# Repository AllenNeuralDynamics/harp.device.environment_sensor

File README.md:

A self-contained, harp-compliant environment sensor

## Features
* pressure sensing
* temperature sensing
* humidity sensing
* USB powered
* Harp synchronization input

## Wiring Diagram
TODO

### Device Pinout
TODO

### Wiring Diagram
TODO

## Theory of Operation
TODO: awesome diagram {here}

## Harp Register Map
[List of Registers](./firmware/docs/register_map.csv)

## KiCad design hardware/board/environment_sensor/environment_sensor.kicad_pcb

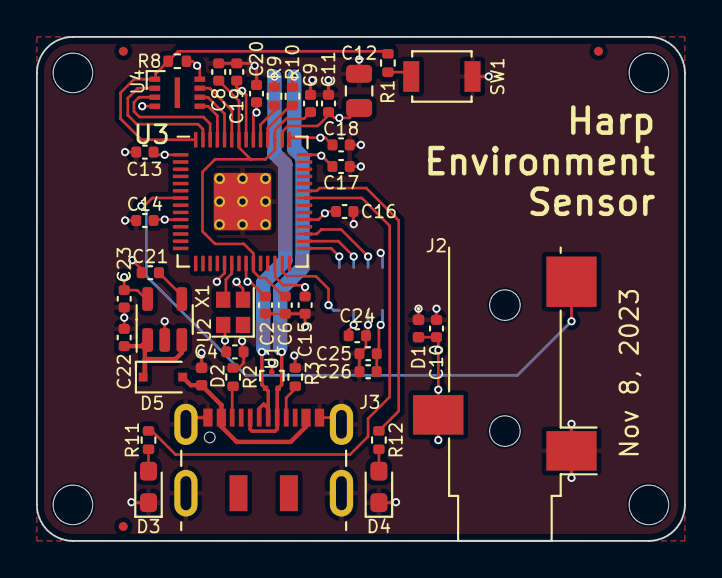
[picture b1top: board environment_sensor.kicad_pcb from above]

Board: 4 copper layers, 36.0 x 28.0 mm, 47 parts (1 on the bottom side), 29 nets.

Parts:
C2, C6, C8, C13, C14, C15, C16, C17, C18, C19, C20, C24, C25: 100nF; C_0402_1005Metric
C4, C21: 10nF; C_0402_1005Metric
C9, C10, C11, C22, C26: 1uF; C_0402_1005Metric
C12: 10uF; C_0805_2012Metric
C23: 2.2uF; C_0402_1005Metric
D1, D2: D_TVS; D_0402_1005Metric
D3, D4: LED; LED_0603_1608Metric_Pad1.05x0.95mm_HandSolder
D5: BAT54J; D_SOD-323F
FID1, FID2, FID3: Fiducial; Fiducial_0.5mm_Mask1mm
J2: AudioJack3; Jack_3.5mm_CUI_SJ-3523-SMT_Horizontal
J3: USB_C_Receptacle_USB2.0; USB_C_Receptacle_JAE_DX07S016JA1R1500
R1: 1K; R_0402_1005Metric
R2, R3: 5K1; R_0402_1005Metric
R8: 10K; R_0402_1005Metric
R9, R10: 27; R_0402_1005Metric
R11, R12: 330; R_0402_1005Metric
SW1: SW_Push; SW_SPST_B3U-1000P
U1: TPD2EUSB30; Texas_DRT-3
U2: LP2985-3.3; SOT-23-5
U3: RP2040; RP2040-QFN-56
U4: W25Q16JVUXIQ; Winbond-8USON-2x3mm
U5: BME688; Bosch_LGA-8_3x3mm_P0.8mm_ClockwisePinNumbering
X1: ECS-TXO-2016; Crystal_SMD_2016-4Pin_2.0x1.6mm

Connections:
+1V1: C6.2, C8.2, C9.1, U3.23 (DVDD), U3.45 (VREG_VOUT), U3.50 (DVDD)
+3V3: C2.2, C4.2, C10.1, C11.1, C12.1, C13.2, C14.2, C15.2, C16.2, C17.2, C18.2, C19.2, C20.2, C23.2, C24.2, C25.2, C26.1, D1.2 (A2), J2.R, R8.2, U2.5 (VOUT), U3.1 (IOVDD), U3.10 (IOVDD), U3.22 (IOVDD), U3.26 (RUN), U3.33 (IOVDD), U3.42 (IOVDD), U3.43 (ADC_AVDD), U3.44 (VREG_IN), U3.48 (USB_VDD), U3.49 (IOVDD), U4.8 (VCC), U5.6 (VDDIO), U5.8 (VDD), X1.4 (VDD)
/Harp Core RP2040 + USB/CS: U3.31 (GPIO20), U5.2 (CSB)
/Harp Core RP2040 + USB/D+: J3.A6 (D+), J3.B6 (D+), R9.2, U1.1 (D+)
/Harp Core RP2040 + USB/D-: J3.A7 (D-), J3.B7 (D-), R10.2, U1.2 (D-)
/Harp Core RP2040 + USB/HARP_CLK_SYNC: J2.T, U3.7 (GPIO5)
/Harp Core RP2040 + USB/PICO: U3.30 (GPIO19), U5.3 (SDI)
/Harp Core RP2040 + USB/POCI: U3.27 (GPIO16), U5.5 (SDO)
/Harp Core RP2040 + USB/QSPI_CLK: U3.52 (QSPI_SCLK), U4.6 (CLK)
/Harp Core RP2040 + USB/QSPI_CS: R1.2, R8.1, U3.56 (QSPI_SS), U4.1 (~CS)
/Harp Core RP2040 + USB/QSPI_D0: U3.53 (QSPI_SD0), U4.5 (DI(IO0))
/Harp Core RP2040 + USB/QSPI_D1: U3.55 (QSPI_SD1), U4.2 (DO(IO1))
/Harp Core RP2040 + USB/QSPI_D2: U3.54 (QSPI_SD2), U4.3 (IO2)
/Harp Core RP2040 + USB/QSPI_D3: U3.51 (QSPI_SD3), U4.7 (IO3)
/Harp Core RP2040 + USB/SCK: U3.29 (GPIO18), U5.4 (SCK)
/Harp Core RP2040 + USB/USB_Boot: R1.1, SW1.2
GND: C2.1, C4.1, C6.1, C8.1, C9.2, C10.2, C11.2, C12.2, C13.1, C14.1, C15.1, C16.1, C17.1, C18.1, C19.1, C20.1, C21.2, C22.2, C23.1, C24.1, C25.1, C26.2, D1.1 (A1), D2.1 (A1), D3.1 (K), D4.1 (K), J2.S, J3.A1 (GND), J3.A12 (GND), J3.B1 (GND), J3.B12 (GND), J3.S1 (SHIELD), R2.2, R3.2, SW1.1, U1.3 (GND), U2.2 (GND), U3.19 (TESTEN), U3.57 (GND), U4.4 (GND), U5.1 (GND), U5.7 (GND), X1.2 (GND)
unnamed: D3.2 (A), R11.2
unnamed: D4.2 (A), R12.2
unnamed: J3.A5 (CC1), R2.1
unnamed: J3.B5 (CC2), R3.1
unnamed: C21.1, U2.4 (BP)
unnamed: R11.1, U3.36 (GPIO24)
unnamed: R12.1, U3.37 (GPIO25)
unnamed: R10.1, U3.46 (USB_DM)
unnamed: R9.1, U3.47 (USB_DP)
unnamed: U3.20 (XIN), X1.3 (OUT)
VBUS: D2.2 (A2), D5.2 (A), J3.A4 (VBUS), J3.A9 (VBUS), J3.B4 (VBUS), J3.B9 (VBUS)
VDD: C22.1, D5.1 (K), U2.1 (VIN), U2.3 (ON/~OFF)

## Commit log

2023-09-06 draft v0.1 pcb
2023-11-07 update 3.5mm connector orientation and 3d models
2024-04-12 flesh out environment sensor firmware
2024-04-12 add hardware license
2024-09-13 Add bme68x driver and adapted Adafruit wrapper
2024-09-13 bugfix starting bytes written
2024-10-03 update pcb with thermal considerations
2024-10-04 update pcb thermal landing
2024-10-08 Integrate harp app/registers & read sensor from core1
2024-10-08 Add simple pyharp interface
2024-10-09 update CUI -> Same Sky
2024-10-10 Add aggregate register & event
2024-10-10 clean up code
2024-10-10 Fix reset behavior & empower enable_sensor_dispatch_events
